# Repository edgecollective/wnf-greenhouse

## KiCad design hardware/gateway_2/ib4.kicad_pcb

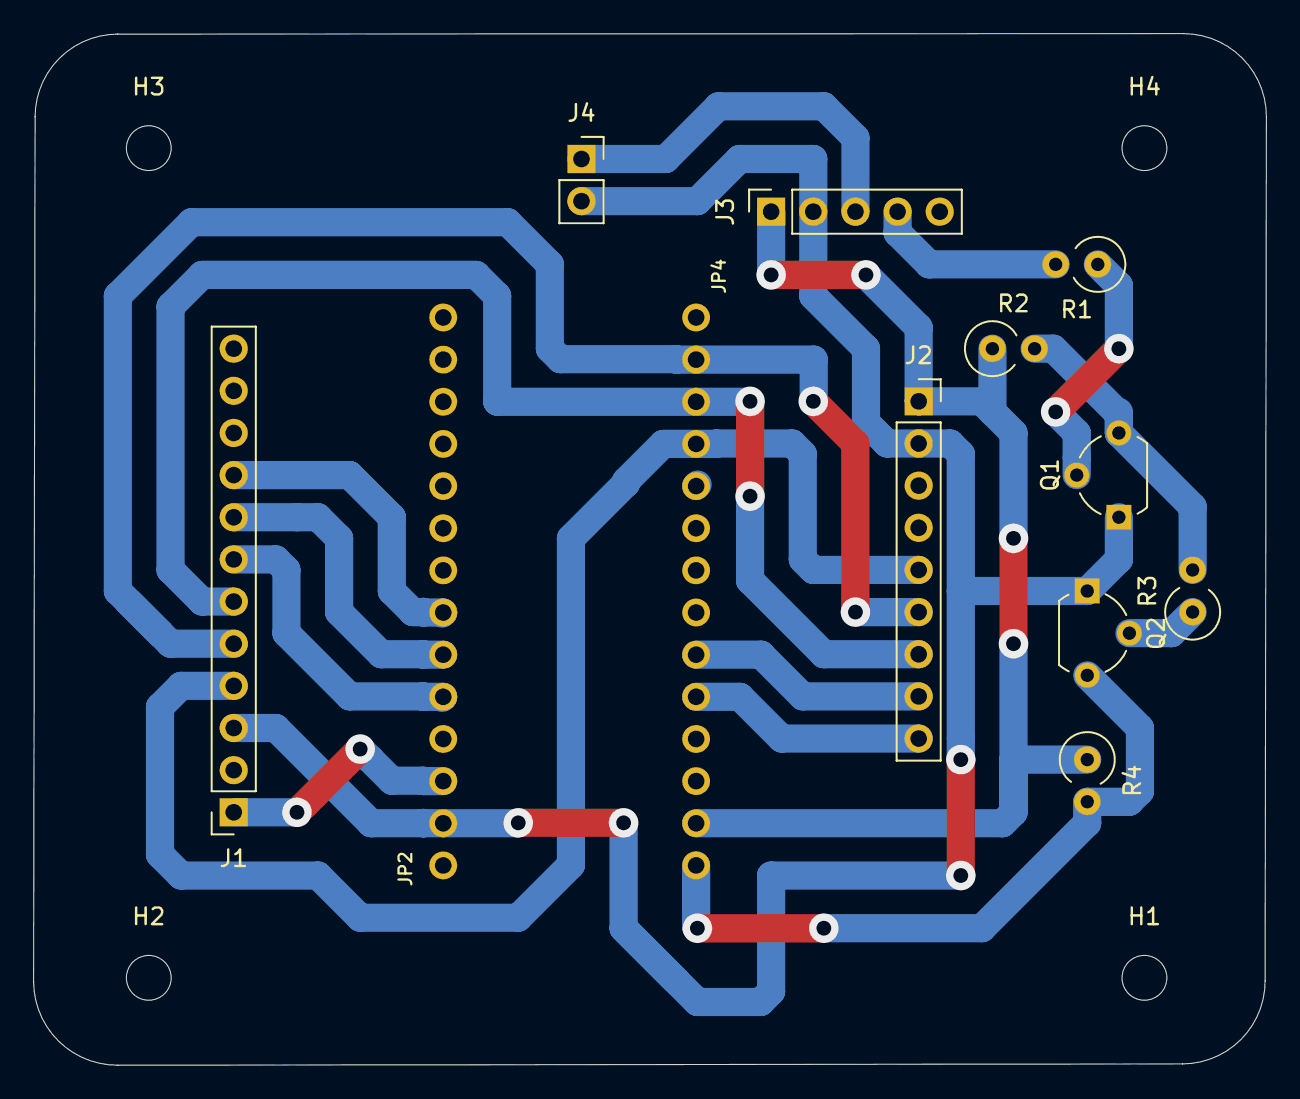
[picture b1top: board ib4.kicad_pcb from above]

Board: 4 copper layers, 74.3 x 62.2 mm, 16 parts (0 on the bottom side), 17 nets.

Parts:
H1, H2, H3, H4: MountingHole; MountingHole_2.7mm_M2.5
J1: Conn_01x12_Female; PinSocket_1x12_P2.54mm_Vertical
J2: Conn_01x09_Female; PinSocket_1x09_P2.54mm_Vertical
J3: Conn_01x05_Female; PinSocket_1x05_P2.54mm_Vertical
J4: Conn_01x02_Female; PinSocket_1x02_P2.54mm_Vertical
JP2, JP4: HEADER-1X14; 1X14_ROUND70
Q1, Q2: Q_NPN_EBC; TO-92L_Wide
R1, R2, R3, R4: R; R_Axial_DIN0309_L9.0mm_D3.2mm_P2.54mm_Vertical

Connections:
+3V3: J2.1, J3.1, JP4.13, R2.1, R4.1
/A0: J2.9, JP4.10
/A1: J2.8, JP4.9
DRV: J3.4, R1.2
E_BUSY: J1.8, JP2.6
E_CS: J1.7, JP2.5
E_~RST: J1.9, JP2.7
GND: J1.3, J2.2, J3.2, J4.2, JP2.2, Q1.1, Q2.1
MISO: J1.5, J2.6, JP4.2
MOSI: J1.6, J2.7, JP4.3
unnamed: J3.3, J4.1
unnamed: Q1.2, R1.1
unnamed: Q1.3, R2.2, R3.2
unnamed: Q2.2, R3.1
SCK: J1.4, J2.5, JP4.4
VBUS: J1.1, JP2.3
~RST: JP4.14, Q2.3, R4.2

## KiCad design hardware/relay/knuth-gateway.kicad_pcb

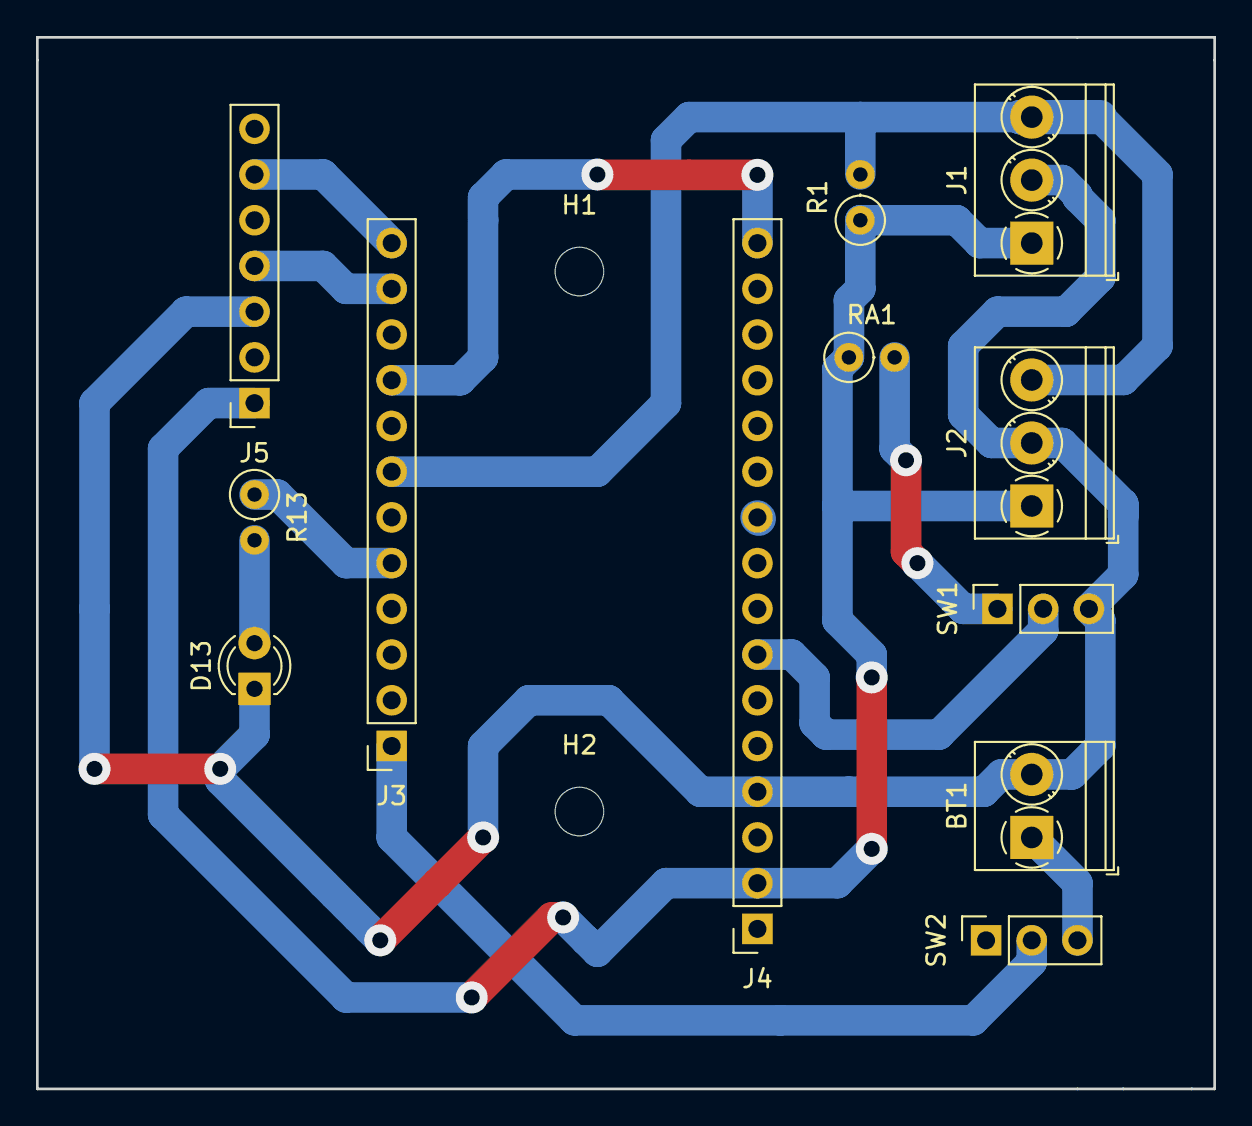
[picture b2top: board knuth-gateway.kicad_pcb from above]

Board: 2 copper layers, 65.4 x 58.4 mm, 14 parts (0 on the bottom side), 12 nets.

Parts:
BT1: Battery; TerminalBlock_Phoenix_PT-1,5-2-3.5-H_1x02_P3.50mm_Horizontal
D13: LED; LED_D3.0mm
H1, H2: MountingHole; MountingHole_2.7mm_M2.5
J1, J2: Screw_Terminal_01x03; TerminalBlock_Phoenix_PT-1,5-3-3.5-H_1x03_P3.50mm_Horizontal
J3: FeatherLora1; PinSocket_1x12_P2.54mm_Vertical
J4: FeatherLora2; PinSocket_1x16_P2.54mm_Vertical
J5: Conn_01x07_Female; PinSocket_1x07_P2.54mm_Vertical
R1: R; R_Axial_DIN0207_L6.3mm_D2.5mm_P2.54mm_Vertical
R13: 1K; R_Axial_DIN0207_L6.3mm_D2.5mm_P2.54mm_Vertical
RA1: R; R_Axial_DIN0207_L6.3mm_D2.5mm_P2.54mm_Vertical
SW1, SW2: SW_SPDT; PinSocket_1x03_P2.54mm_Vertical

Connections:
+3V3: J1.1, J2.1, J4.2, J5.1, R1.1, RA1.1
A2: J4.7, SW1.2
D6: J3.9, J4.16
D10: J1.3, J2.3, J3.7, R1.2
D12: J3.5, R13.1
GND: BT1.2, D13.1, J1.2, J2.2, J4.4, J5.3, SW1.3
unnamed: BT1.1, SW2.3
unnamed: D13.2, R13.2
unnamed: RA1.2, SW1.1
SCL: J3.11, J5.4
SDA: J3.12, J5.6
VBAT: J3.1, SW2.2

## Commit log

2020-06-05 update;
2020-06-14 increased temperature resolution of onewire from 9 to 12
2020-06-14 shrortened jumper wires
2020-09-02 Bump bl from 4.0.2 to 4.0.3 in /ver_0.1/node_reader
    Bumps [bl](https://github.com/rvagg/bl) from 4.0.2 to 4.0.3.
    - [Release notes](https://github.com/rvagg/bl/releases)
    - [Commits](https://github.com/rvagg/bl/compare/v4.0.2...v4.0.3)
2020-12-12 Bump ini from 1.3.5 to 1.3.8 in /ver_0.1/node_reader
    Bumps [ini](https://github.com/isaacs/ini) from 1.3.5 to 1.3.8.
    - [Release notes](https://github.com/isaacs/ini/releases)
    - [Commits](https://github.com/isaacs/ini/compare/v1.3.5...v1.3.8)
2022-02-13 Bump ajv from 6.12.2 to 6.12.6 in /ver_0.1/node_reader
    Bumps [ajv](https://github.com/ajv-validator/ajv) from 6.12.2 to 6.12.6.
    - [Release notes](https://github.com/ajv-validator/ajv/releases)
    - [Commits](https://github.com/ajv-validator/ajv/compare/v6.12.2...v6.12.6)
    ---
    updated-dependencies:
    - dependency-name: ajv
2022-03-26 Bump minimist from 1.2.5 to 1.2.6 in /ver_0.1/node_reader
    Bumps [minimist](https://github.com/substack/minimist) from 1.2.5 to 1.2.6.
    - [Release notes](https://github.com/substack/minimist/releases)
    - [Commits](https://github.com/substack/minimist/compare/1.2.5...1.2.6)
    ---
    updated-dependencies:
    - dependency-name: minimist
2022-12-11 Bump qs from 6.5.2 to 6.5.3 in /ver_0.1/node_reader
    Bumps [qs](https://github.com/ljharb/qs) from 6.5.2 to 6.5.3.
    - [Release notes](https://github.com/ljharb/qs/releases)
    - [Changelog](https://github.com/ljharb/qs/blob/main/CHANGELOG.md)
    - [Commits](https://github.com/ljharb/qs/compare/v6.5.2...v6.5.3)
    ---
    updated-dependencies:
